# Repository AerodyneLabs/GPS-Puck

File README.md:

GPS-Puck
========

Venus based GPS serial GPS puck

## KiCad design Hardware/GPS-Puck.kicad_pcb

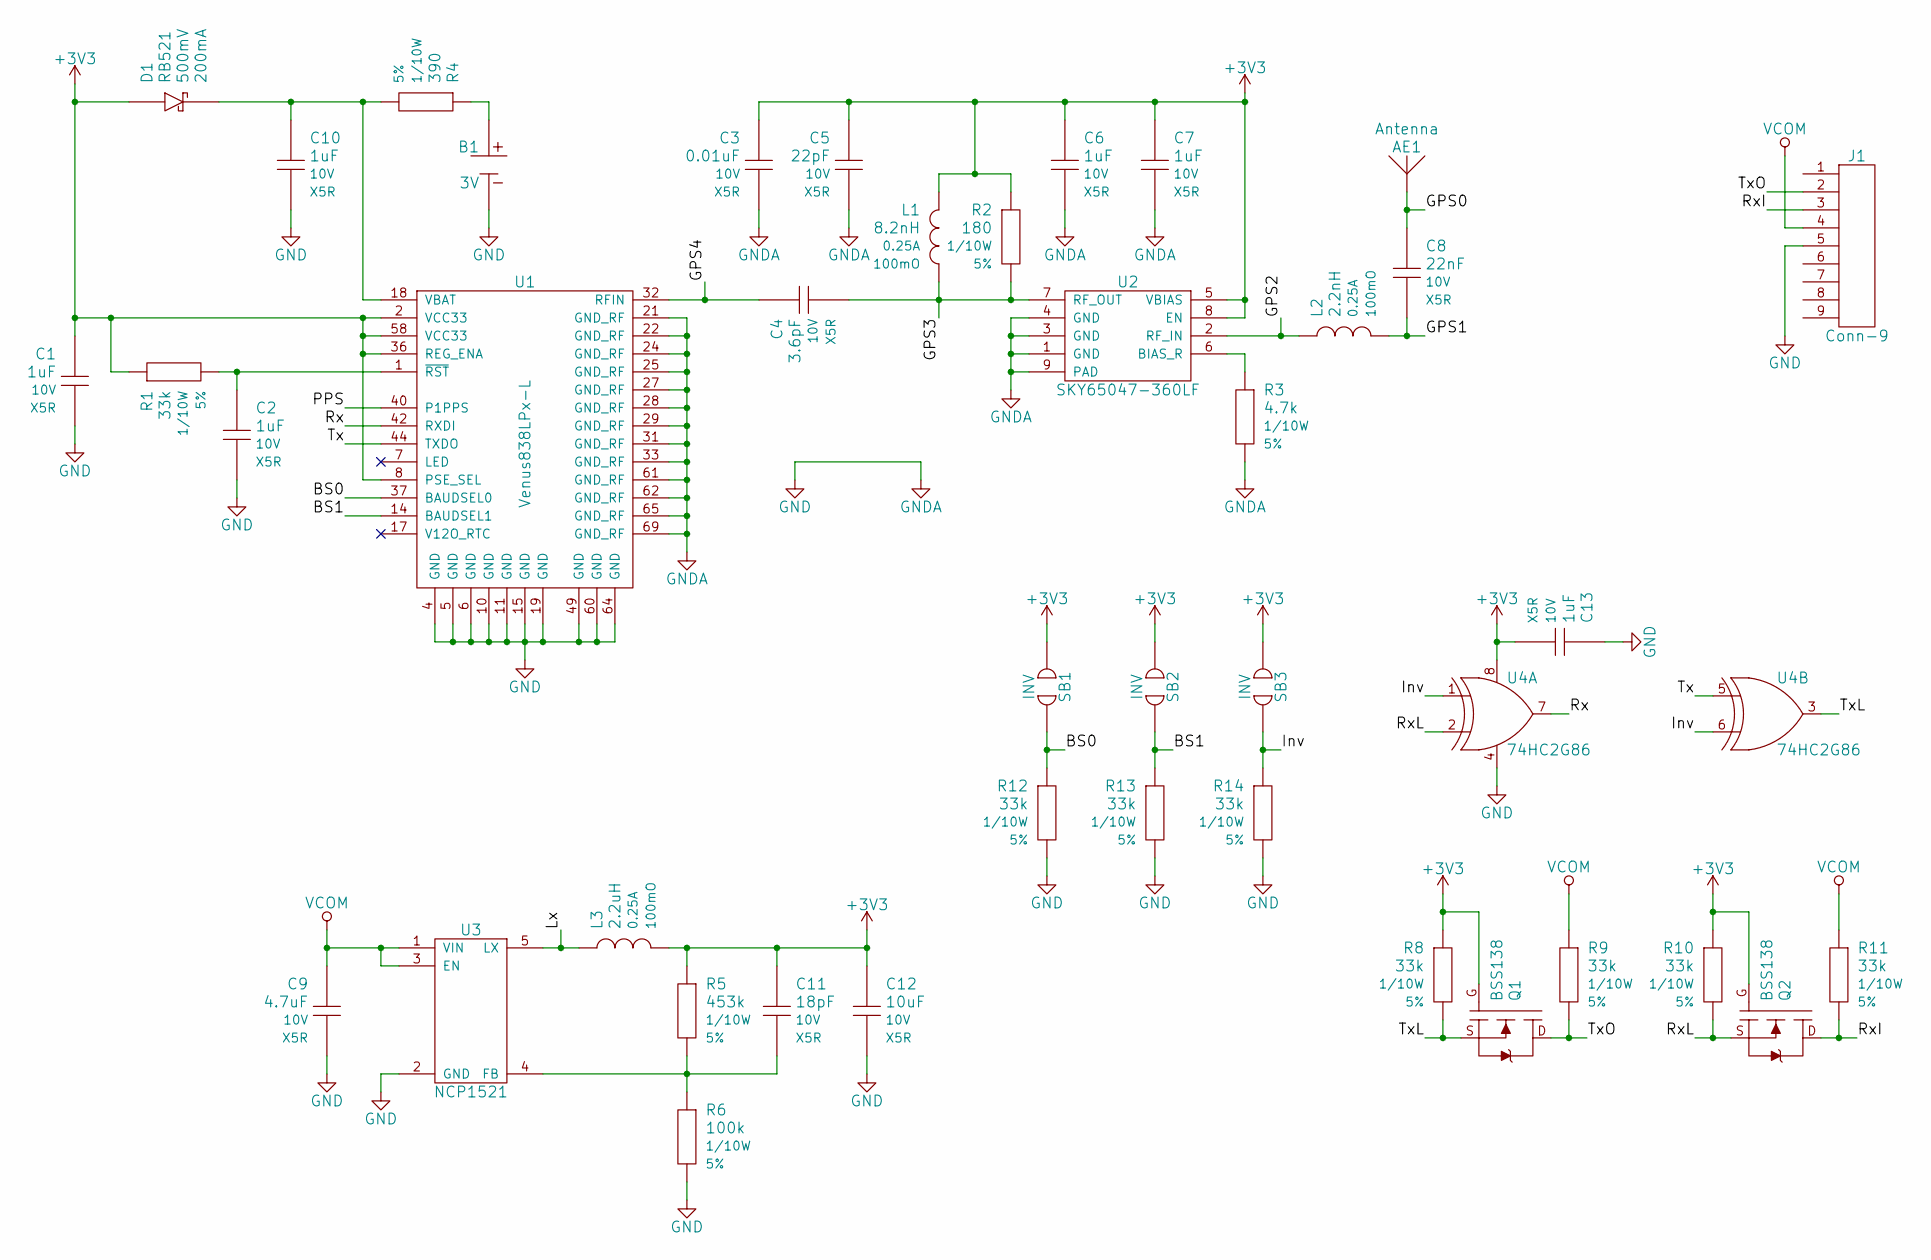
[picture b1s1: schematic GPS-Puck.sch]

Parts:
AE1: Antenna; Antenna_APAE1575R1840BADB1F
B1: 3V; Battery_ML-1220-F1AN; Manufacturer Part # ML-1220/F1AN
C1, C2, C6, C7, C10, C13: 1uF; CAPC1608N; Voltage 10V; Manufacturer Part # Value
C3: 0.01uF; CAPC1608N; Voltage 10V; Manufacturer Part # Value
C4: 3.6pF; CAPC1608N; Voltage 10V; Manufacturer Part # Value
C5: 22pF; CAPC1608N; Voltage 10V; Manufacturer Part # Value
C8: 22nF; CAPC1608N; Voltage 10V; Manufacturer Part # Value
C9: 4.7uF; CAPC1608N; Voltage 10V; Manufacturer Part # Value
C11: 18pF; CAPC1608N; Voltage 10V; Manufacturer Part # Value
C12: 10uF; CAPC2012N; Voltage 10V; Manufacturer Part # Value
D1: RB521; SODFL1608N; Forward Voltage 500mV; Reverse Voltage 30V; Manufacturer Part # RB521S30T1G
J1: Conn-9; Conn_9-Wire-Pads
L1: 8.2nH; INDC1608N; Manufacturer Part # Value
L2: 2.2nH; INDC1608N; Manufacturer Part # Value
L3: 2.2uH; INDC2012N; Manufacturer Part # Value
Q1, Q2: BSS138; SOT95P240-3N-GSD
R1, R8, R9, R10, R11, R12, R13, R14: 33k; RESC1608N; Tolerance 5%; Manufacturer Part # Value
R2: 180; RESC1608N; Tolerance 5%; Manufacturer Part # Value
R3: 4.7k; RESC1608N; Tolerance 5%; Manufacturer Part # Value
R4: 390; RESC1608N; Tolerance 5%; Manufacturer Part # Value
R5: 453k; RESC1608N; Tolerance 5%; Manufacturer Part # Value
R6: 100k; RESC1608N; Tolerance 5%; Manufacturer Part # Value
SB1, SB2, SB3: INV; SB1608N; Manufacturer Part # Value
U1: Venus838LPx-L; Sensor_Venus838
U2: SKY65047-360LF; SON50P200X200-9T100X180N
U3: NCP1521; SOT95P275-5L40N
U4: 74HC2G86; SOP65P400-8N; Manufacturer Part # 74HC2G86DP,125

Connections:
+3V3: C1.1, C3.1, C5.1, C6.1, C7.1, C11.1, C12.1, C13.2, D1.A, L1.1, L3.2, Q1.G, Q2.G, R1.1, R2.1, R5.1, R8.1, R10.1, SB1.1, SB2.1, SB3.1, U1.2 (VCC33), U1.8 (PSE_SEL), U1.36 (REG_ENA), U1.58 (VCC33), U2.5 (VBIAS), U2.8 (EN), U4.8
/BS0: R12.1, SB1.2, U1.37 (BAUDSEL0)
/BS1: R13.1, SB2.2, U1.14 (BAUDSEL1)
/GPS0: AE1.1, C8.1
/GPS1: C8.2, L2.2
/GPS2: L2.1, U2.2 (RF_IN)
/GPS3: C4.2, L1.2, R2.2, U2.7 (RF_OUT)
/GPS4: C4.1, U1.32 (RFIN)
/Inv: R14.1, SB3.2, U4.1, U4.6
/Lx: L3.1, U3.5 (LX)
/PPS: U1.40 (P1PPS)
/Rx: U1.42 (RXDI), U4.7
/RxI: J1.3, Q2.D, R11.2
/RxL: Q2.S, R10.2, U4.2
/Tx: U1.44 (TXDO), U4.5
/TxL: Q1.S, R8.2, U4.3
/TxO: J1.2, Q1.D, R9.2
GND: B1.2, C1.2, C2.2, C3.2, C5.2, C6.2, C7.2, C9.2, C10.2, C12.2, C13.1, J1.5, R3.2, R6.2, R12.2, R13.2, R14.2, U1.4 (GND), U1.5 (GND), U1.6 (GND), U1.10 (GND), U1.11 (GND), U1.15 (GND), U1.19 (GND), U1.21 (GND_RF), U1.22 (GND_RF), U1.24 (GND_RF), U1.25 (GND_RF), U1.27 (GND_RF), U1.28 (GND_RF), U1.29 (GND_RF), U1.31 (GND_RF), U1.33 (GND_RF), U1.49 (GND), U1.60 (GND), U1.61 (GND_RF), U1.62 (GND_RF), U1.64 (GND), U1.65 (GND_RF), U1.69 (GND_RF), U2.1 (GND), U2.3 (GND), U2.4 (GND), U2.9 (PAD), U3.2 (GND), U4.4
unnamed: B1.1, R4.1
unnamed: C2.1, R1.2, U1.1 (~RST)
unnamed: C10.1, D1.C, R4.2, U1.18 (VBAT)
unnamed: C11.2, R5.2, R6.1, U3.4 (FB)
unnamed: R3.1, U2.6 (BIAS_R)
VCOM: C9.1, J1.4, R9.1, R11.1, U3.1 (VIN), U3.3 (EN)

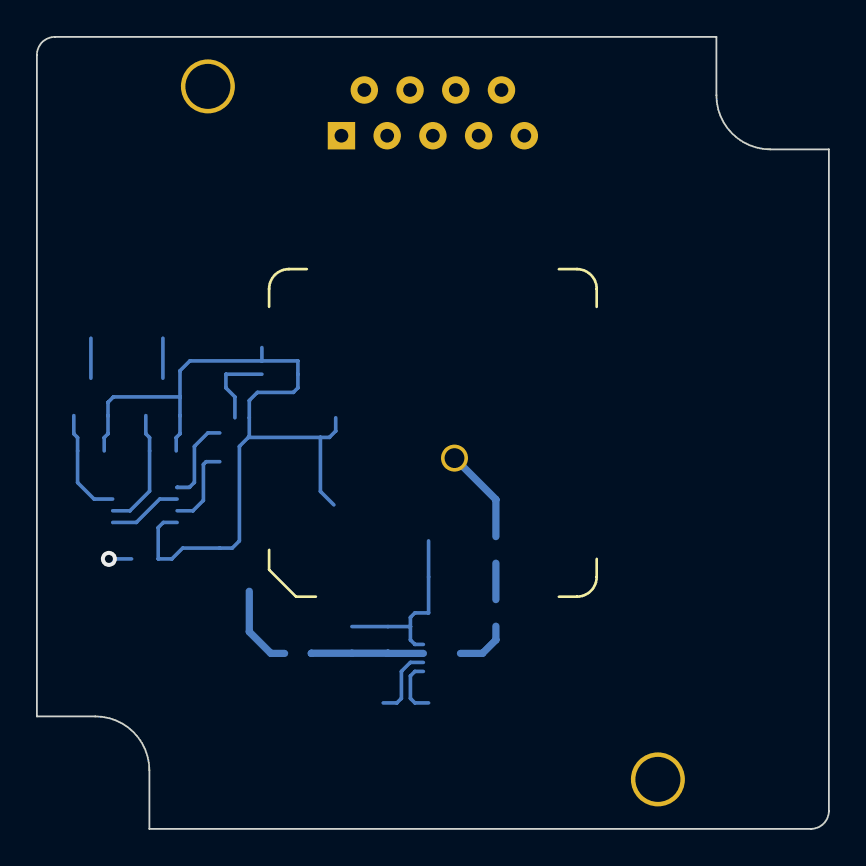
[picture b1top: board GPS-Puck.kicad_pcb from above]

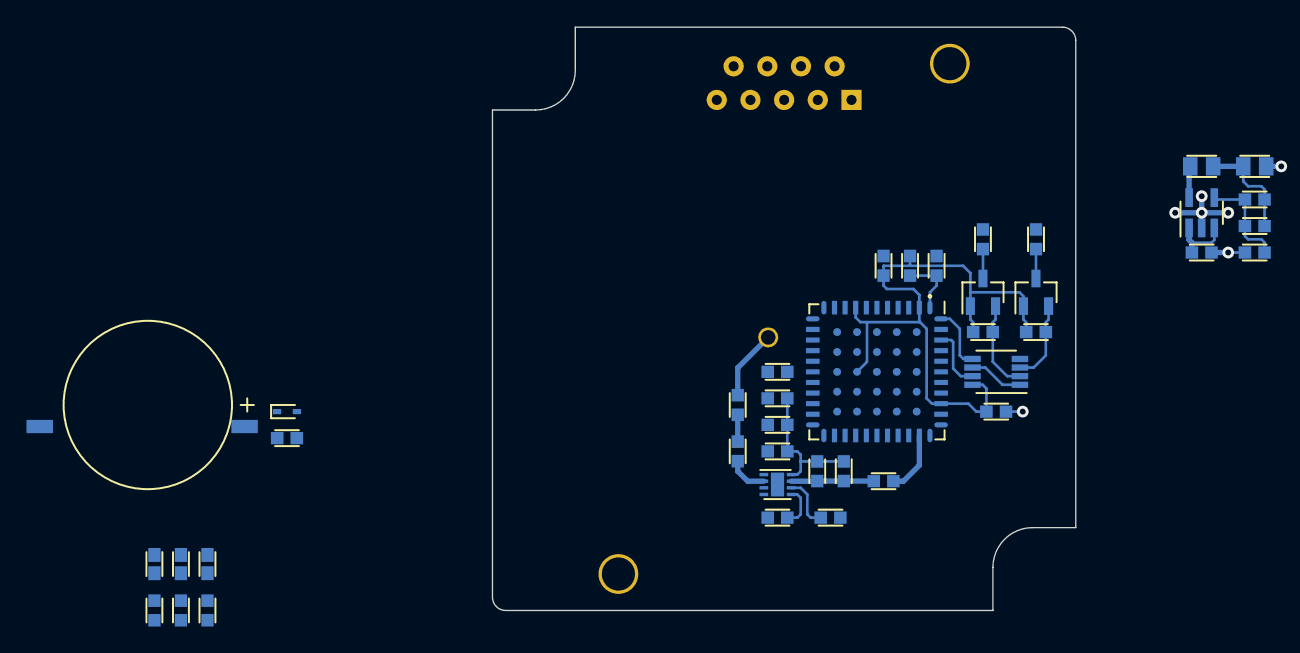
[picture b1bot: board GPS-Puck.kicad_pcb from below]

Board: 2 copper layers, 44.0 x 44.0 mm, 43 parts (41 on the bottom side), 23 nets.

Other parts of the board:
Board_Hammond-1551RFL: Board; Board_Hammond-1551RFL

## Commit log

2015-01-01 Add gitignore
2015-01-02 Datasheets
2015-01-02 GPS and LNA routing
2015-01-02 Routing
2015-01-02 Power schematic
2015-01-02 Rough power layout
2015-01-02 Add wire connector
2015-01-02 Add level translation
    Closes #1
2015-01-02 Add serial inverter
2015-01-02 Add configuration jumpers
2015-01-06 Majority layout and routing

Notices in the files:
Hardware/GPS-Puck.kicad_pcb:
License: CC-BY-SA
